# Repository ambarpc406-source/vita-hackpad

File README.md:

# vita-hackpad
it is a hack pad which uses 6 tactile switches for the keyboard

# THE PCB
the pcb is overall simple and not complecated 

here it is in 3d viewer mode in kicad

# THE SCHEMATICS 
THE SCHEMATICS IN THIS COULD BE A LITTLE CONFUSING AS OF THE LACK OF PLACEMENT

# THE CASE
now the case has to parts one is the top layer and the other is the bottam layer
the top layer

the bottam layer

# THE BOM 
here is the list

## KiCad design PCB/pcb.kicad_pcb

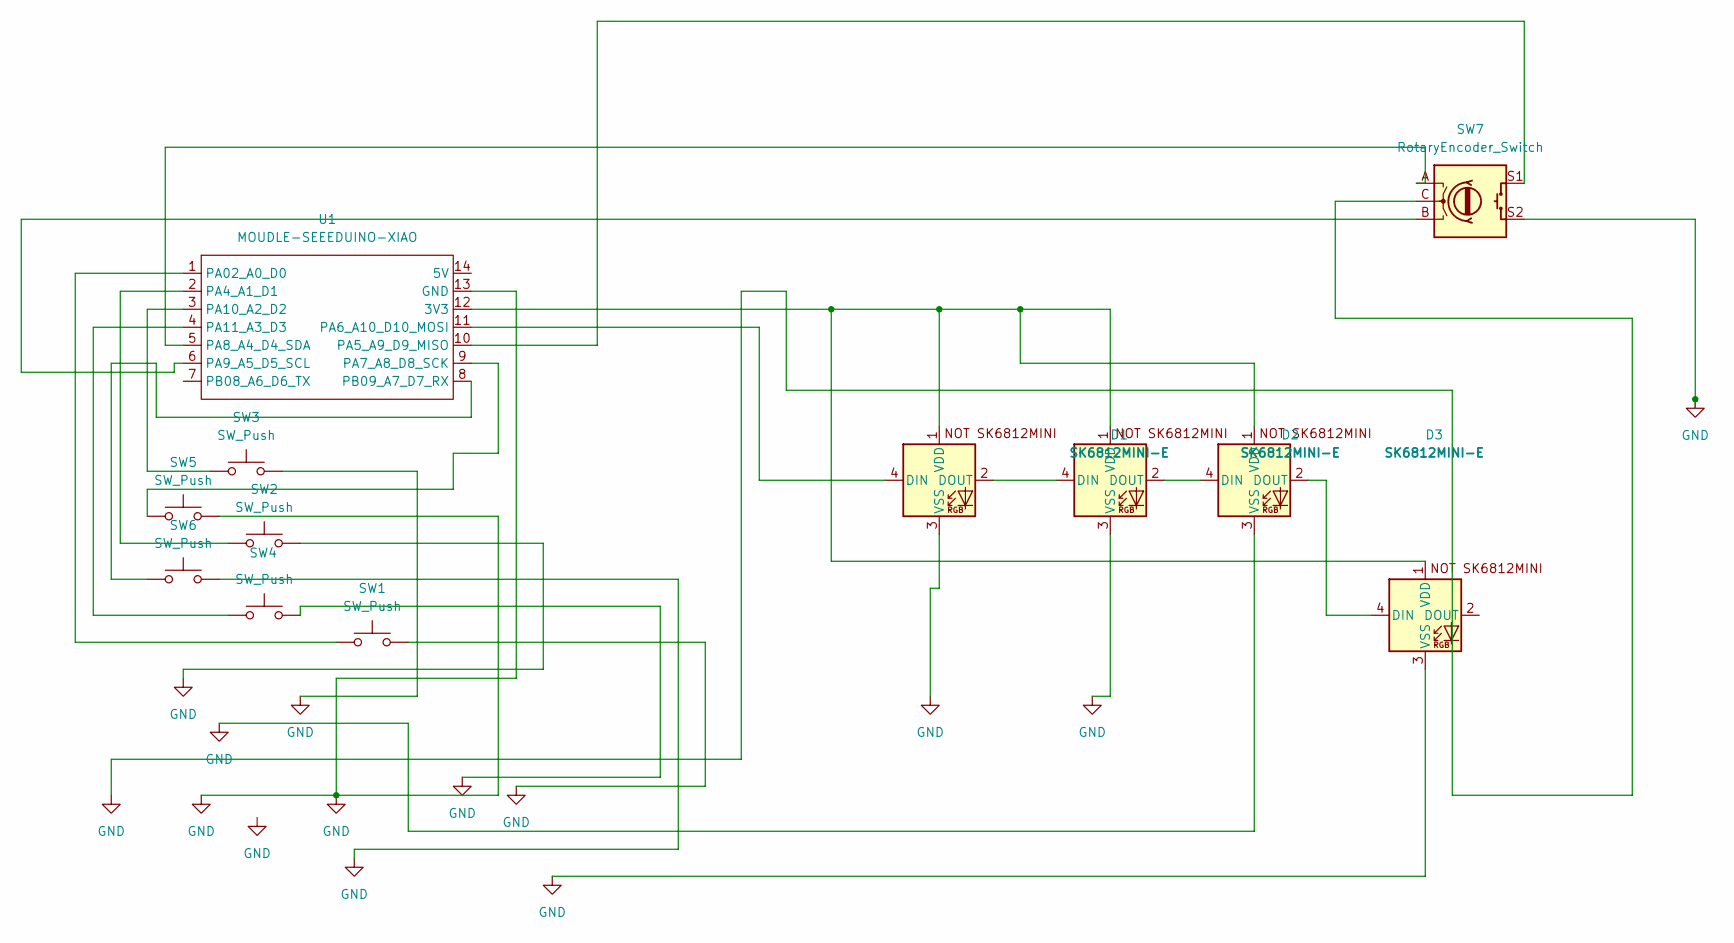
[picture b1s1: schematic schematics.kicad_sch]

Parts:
D1, D2, D3, D4: SK6812MINI-E; SK6812MINI-E_fixed
SW1, SW2, SW3, SW4, SW5, SW6: SW_Push; SW_Cherry_MX_1.00u_PCB
SW7: RotaryEncoder_Switch; RotaryEncoder_Alps_EC11E-Switch_Vertical_H20mm
U1: MOUDLE-SEEEDUINO-XIAO; XIAO-Generic-Hybrid-14P-2.54-21X17.8MM

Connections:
GND: D1.3 (VSS), D2.3 (VSS), D3.3 (VSS), D4.3 (VSS), SW1.2, SW2.2, SW3.2, SW4.2, SW5.2, SW6.2, SW7.C, SW7.S2, U1.13 (GND)
unnamed: D1.4 (DIN), U1.11 (PA6_A10_D10_MOSI)
unnamed: D1.2 (DOUT), D2.4 (DIN)
unnamed: D1.1 (VDD), D2.1 (VDD), D3.1 (VDD), D4.1 (VDD), U1.12 (3V3)
unnamed: D2.2 (DOUT), D3.4 (DIN)
unnamed: D3.2 (DOUT), D4.4 (DIN)
unnamed: SW1.1, U1.1 (PA02_A0_D0)
unnamed: SW2.1, U1.2 (PA4_A1_D1)
unnamed: SW7.S1, U1.10 (PA5_A9_D9_MISO)
unnamed: SW5.1, U1.9 (PA7_A8_D8_SCK)
unnamed: SW7.A, U1.5 (PA8_A4_D4_SDA)
unnamed: SW7.B, U1.6 (PA9_A5_D5_SCL)
unnamed: SW3.1, U1.3 (PA10_A2_D2)
unnamed: SW4.1, U1.4 (PA11_A3_D3)
unnamed: SW6.1, U1.8 (PB09_A7_D7_RX)

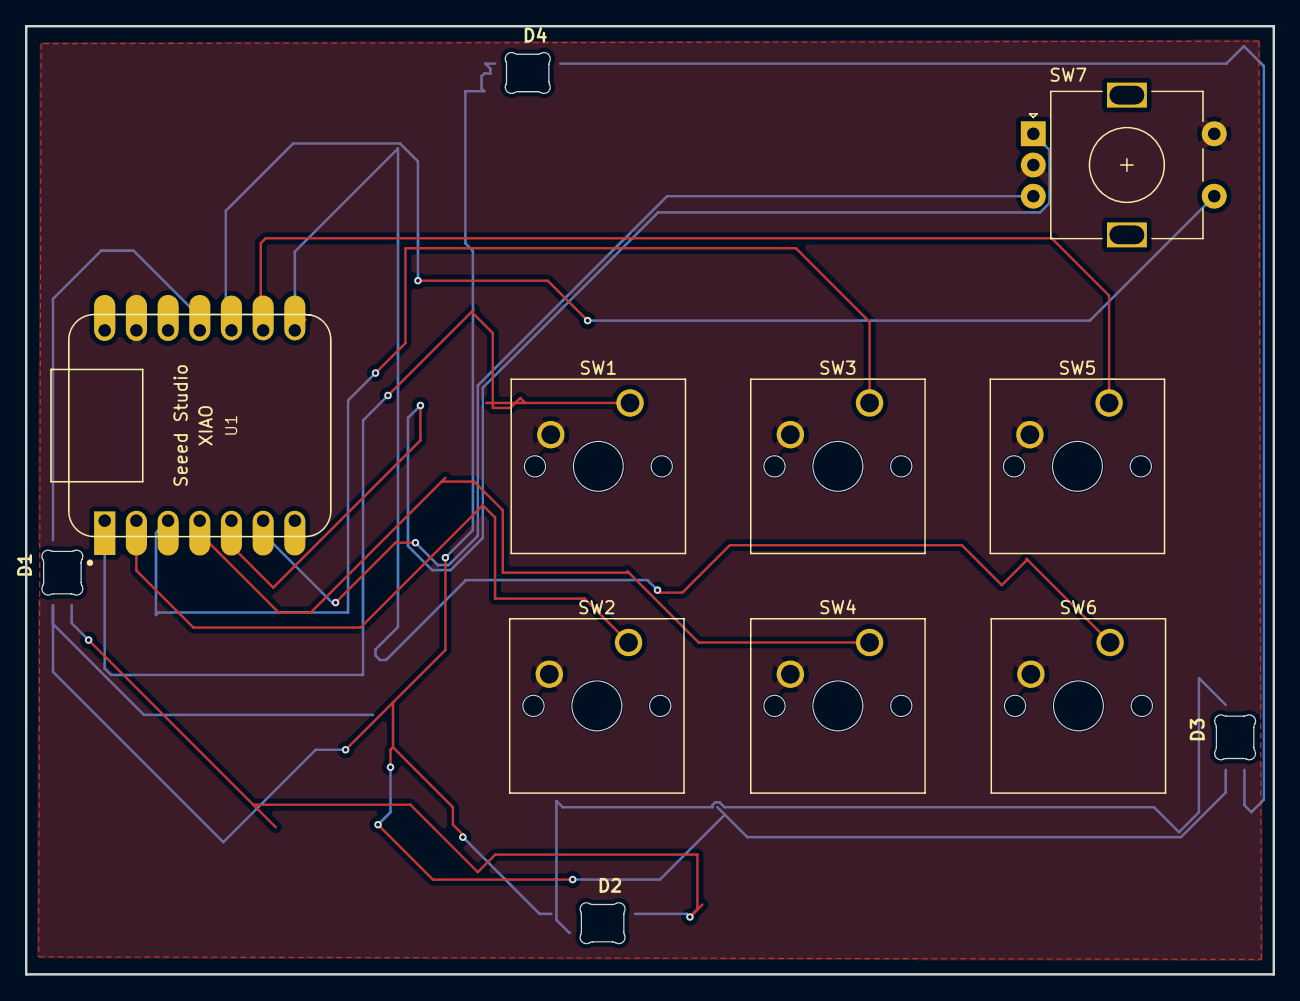
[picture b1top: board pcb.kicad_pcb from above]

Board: 2 copper layers, 100.0 x 76.0 mm, 12 parts (0 on the bottom side), 15 nets.

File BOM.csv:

"Reference","Qty","Value","Footprint","Datasheet"
"D1,D2,D3,D4","4","SK6812MINI-E","hackclub:SK6812MINI-E_fixed","https://cdn-shop.adafruit.com/product-files/4960/4960_SK6812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"
"SW1,SW2,SW3,SW4,SW5,SW6","6","SW_Push","Button_Switch_Keyboard:SW_Cherry_MX_1.00u_PCB",""
"SW7","1","RotaryEncoder_Switch","Rotary_Encoder:RotaryEncoder_Alps_EC11E-Switch_Vertical_H20mm",""
"U1","1","MOUDLE-SEEEDUINO-XIAO","hackclub:XIAO-Generic-Hybrid-14P-2.54-21X17.8MM",""
